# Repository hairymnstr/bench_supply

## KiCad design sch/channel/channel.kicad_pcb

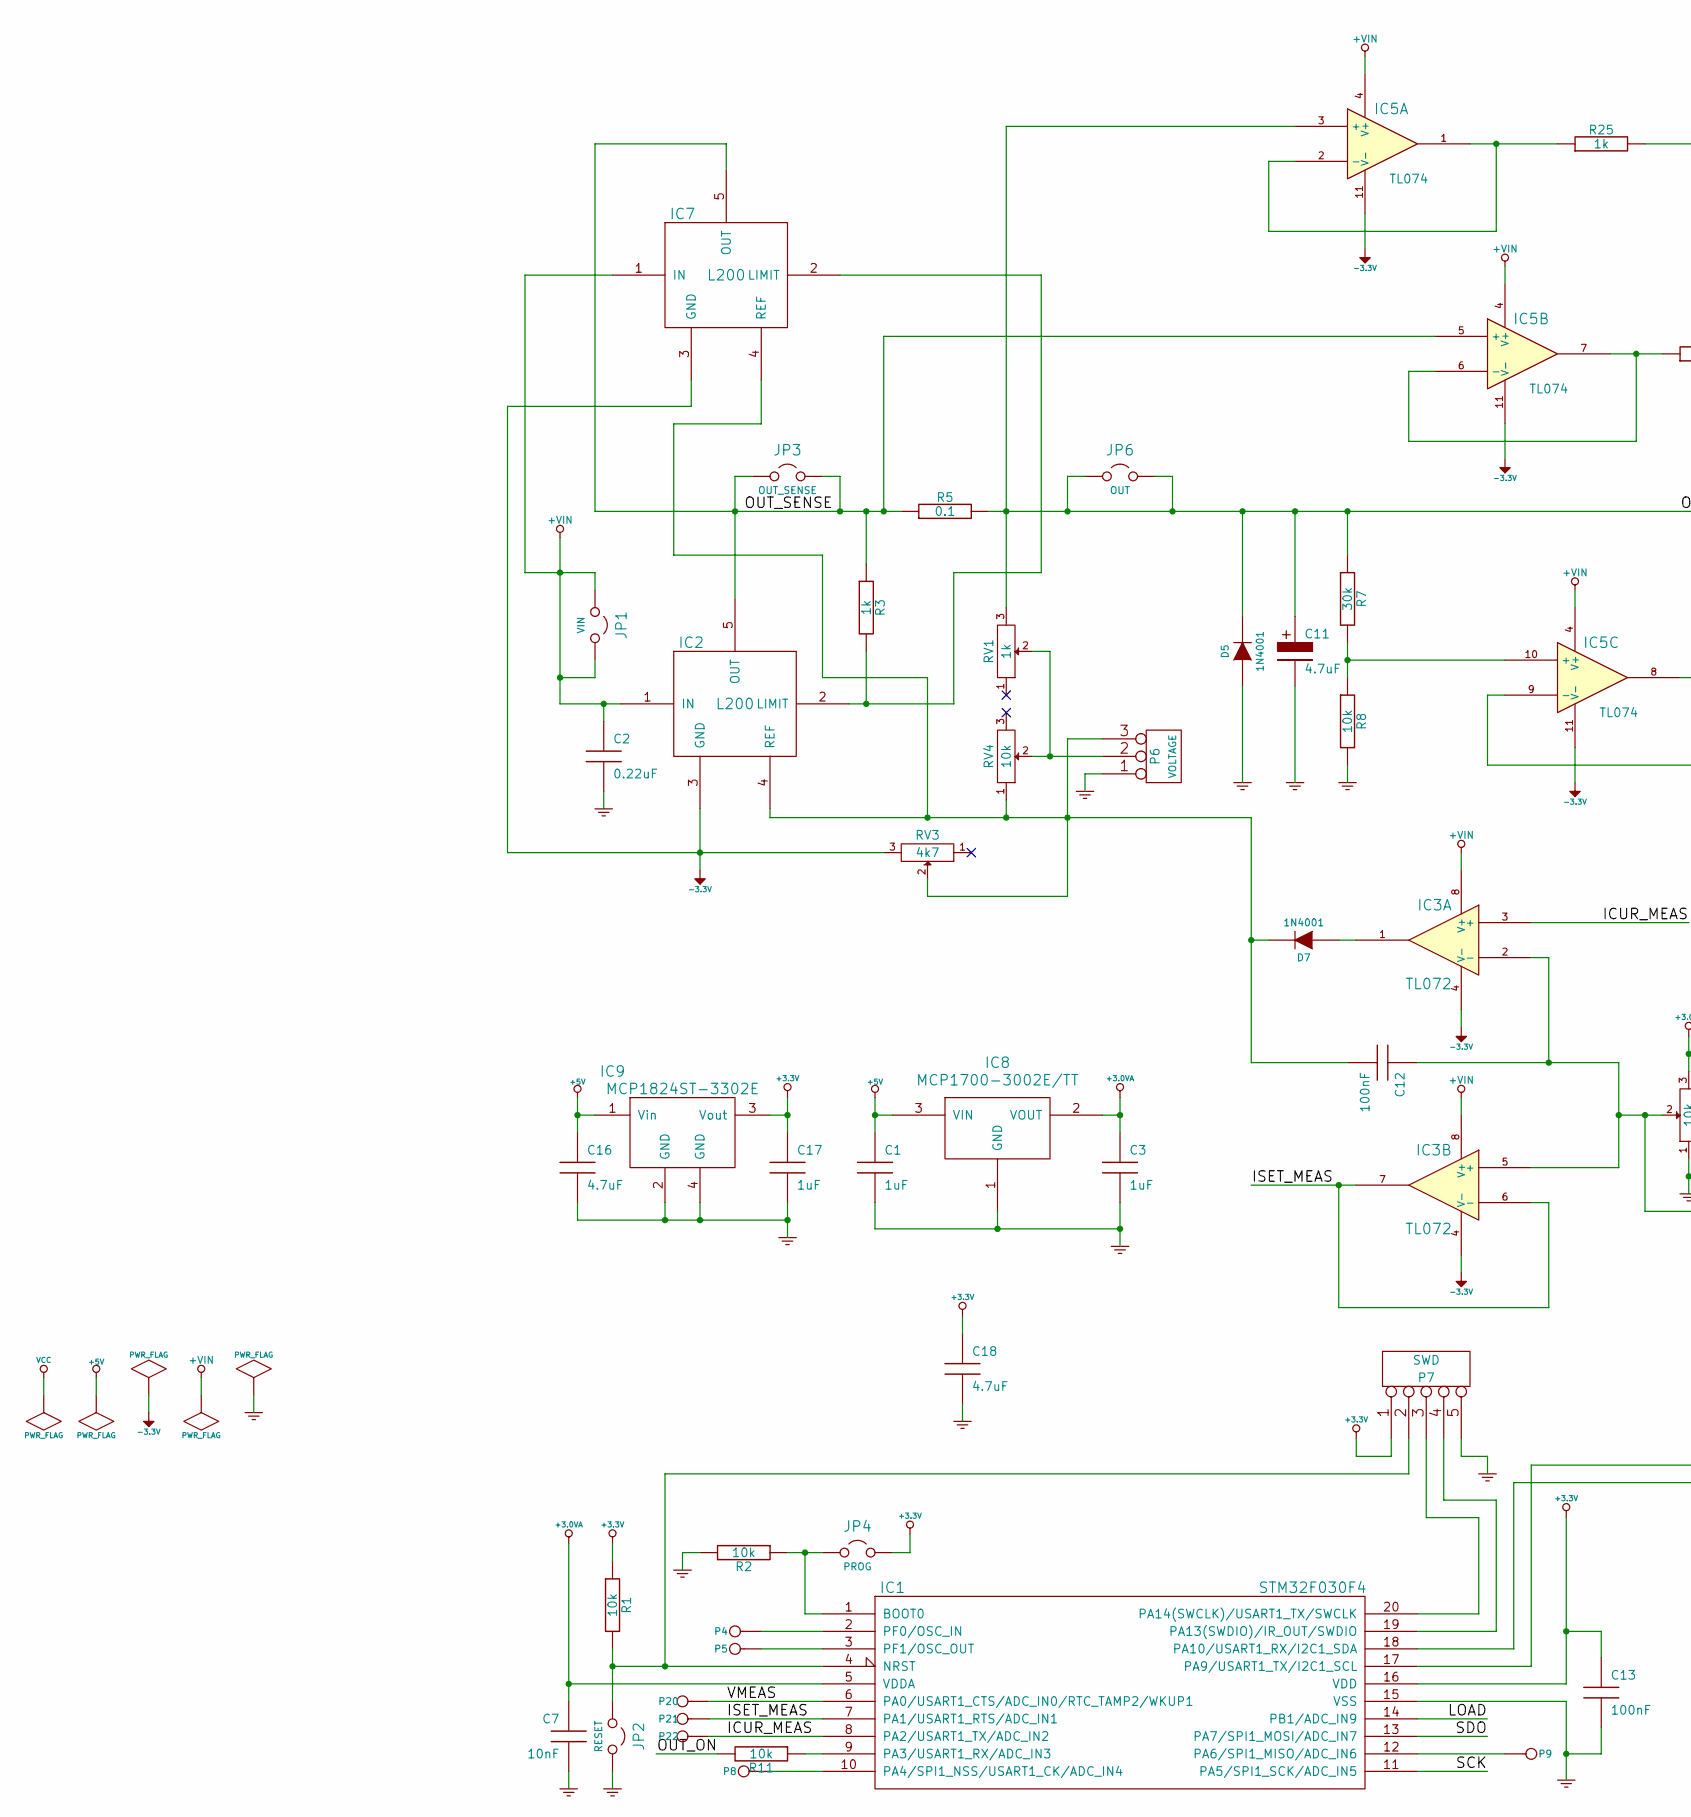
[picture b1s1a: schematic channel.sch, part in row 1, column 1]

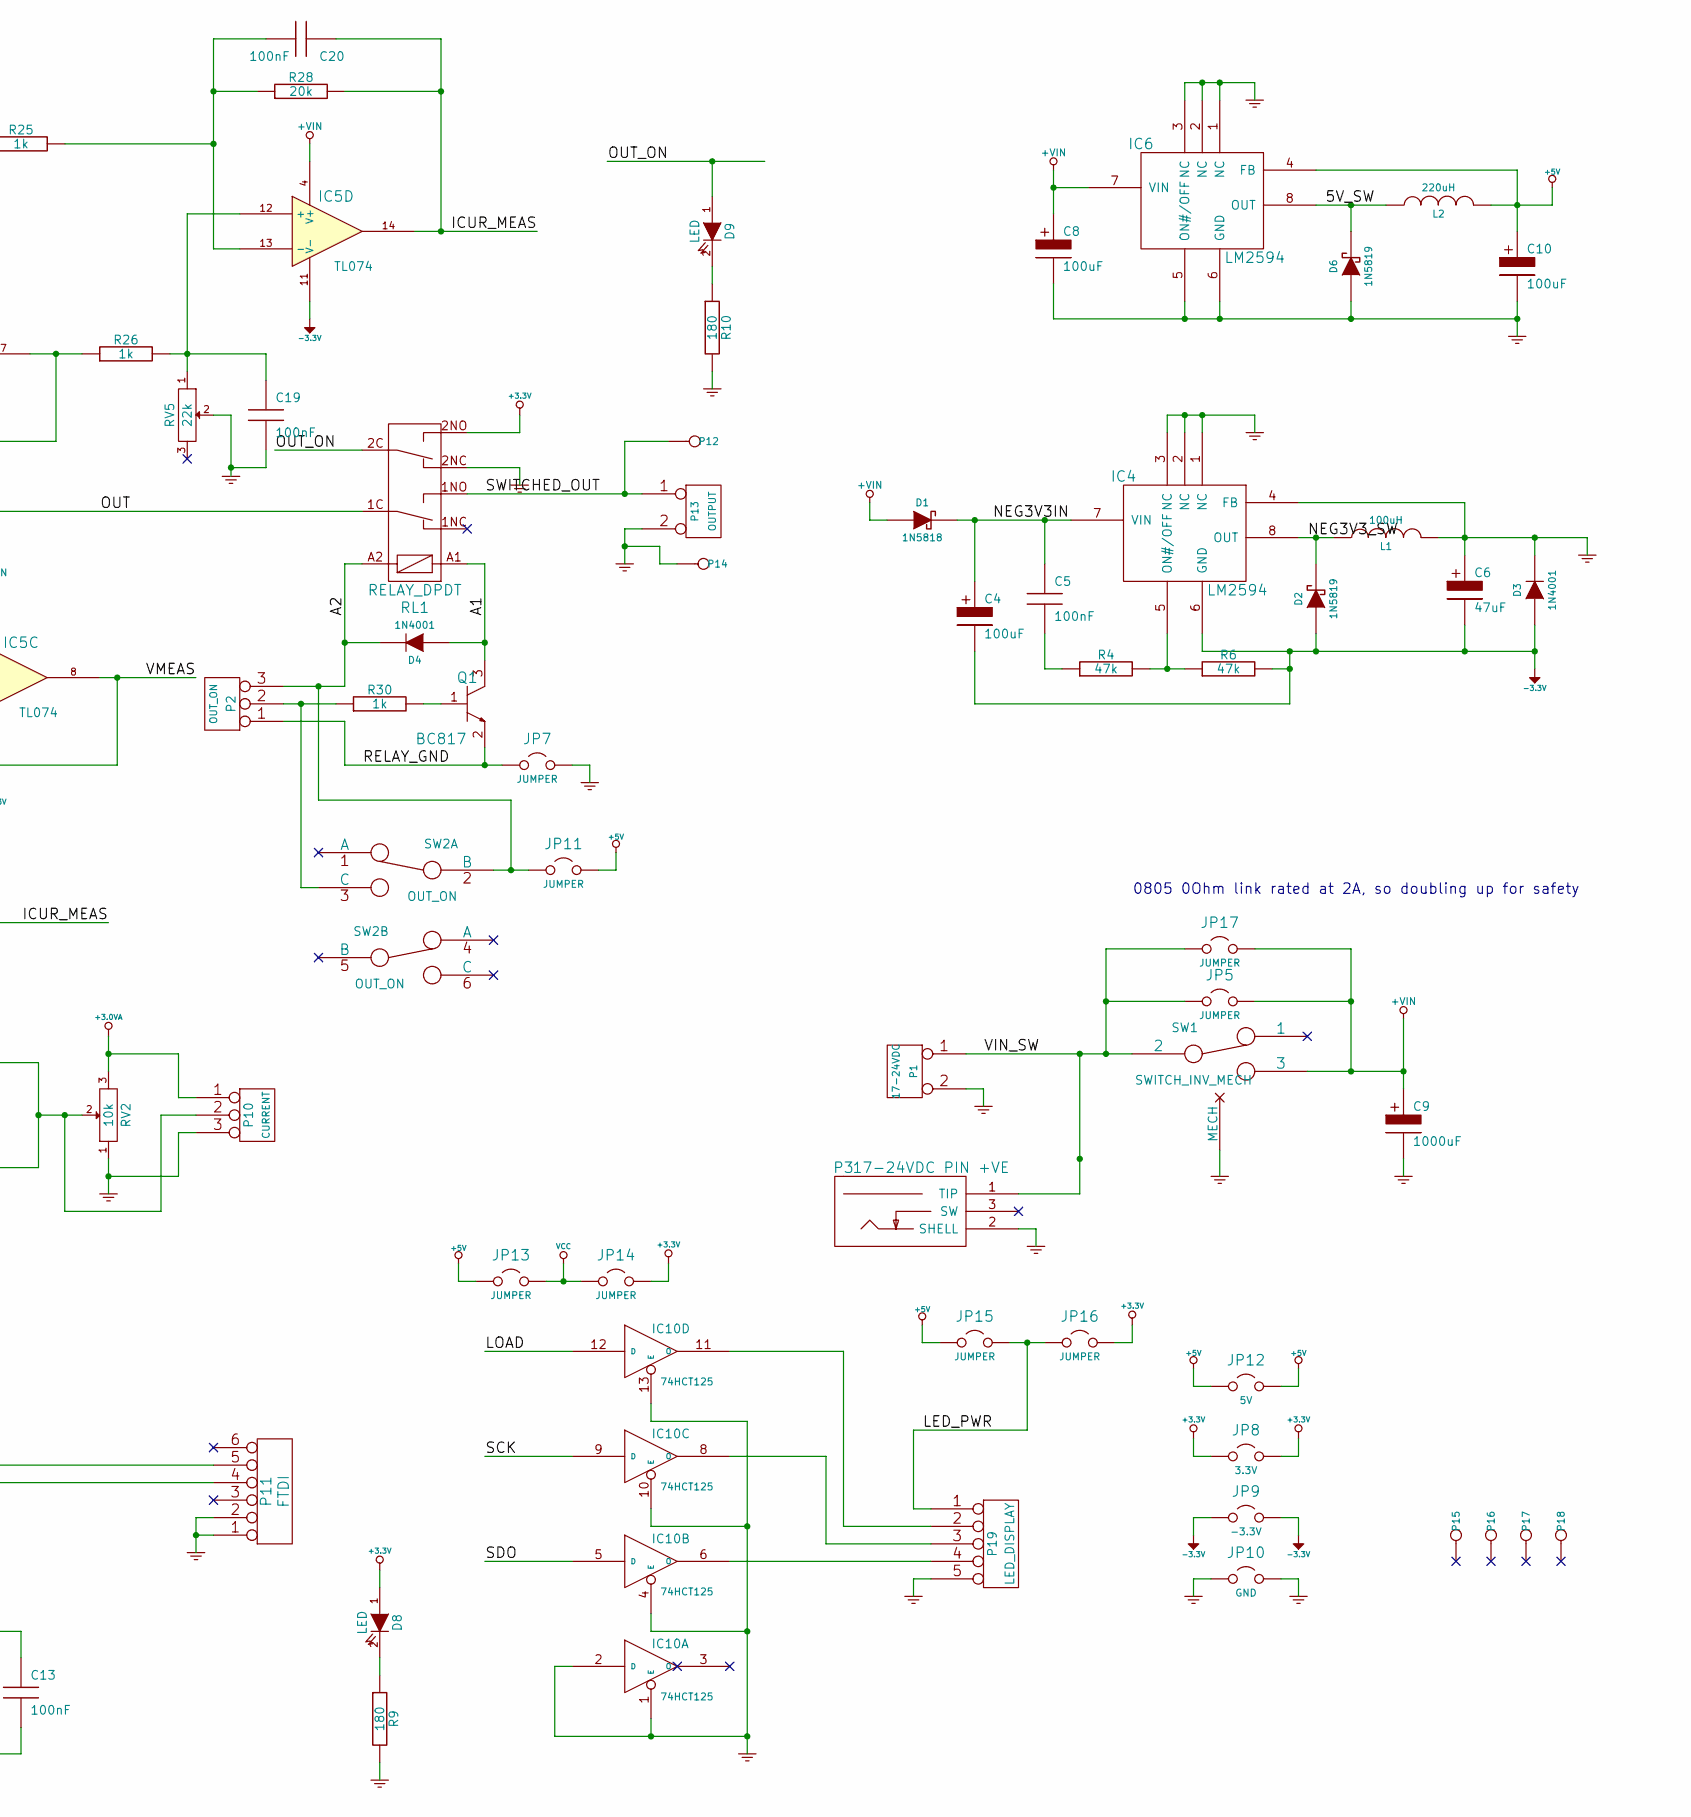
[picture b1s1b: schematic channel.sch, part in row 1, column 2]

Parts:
C1, C3, C17: 1uF
C2: 0.22uF
C4, C8, C10: 100uF
C5, C12, C13, C19, C20: 100nF
C6: 47uF
C7: 10nF
C9: 1000uF
C11, C16, C18: 4.7uF
D1: 1N5818
D2, D6: 1N5819
D3, D4, D5, D7: 1N4001
D8, D9: LED
IC1: STM32F030F4
IC2, IC7: L200
IC3: TL072; Farnell 156-4343
IC4, IC6: LM2594
IC5: TL074; Farnell 959-3349
IC8: MCP1700-3002E/TT
IC9: MCP1824ST-3302E
IC10: 74HCT125; Farnell 120-1306
JP1: VIN
JP2: RESET
JP3: OUT_SENSE
JP4: PROG
JP5, JP7, JP11, JP13, JP14, JP15, JP16, JP17: JUMPER
JP6: OUT
JP8: 3.3V
JP9: -3.3V
JP10: GND
JP12: 5V
L1: 100uH
L2: 220uH
P1: 17-24VDC
P2: OUT_ON
P3: 17-24VDC PIN +VE
P4, P5, P8, P9, P12, P14, P15, P16, P17, P18: CONN_1
P6: VOLTAGE
P7: SWD
P10: CURRENT
P11: FTDI
P13: OUTPUT
P19: LED_DISPLAY
P20: V
P21: I_SET
P22: I_NOW
Q1: BC817
R1, R2, R8, R11: 10k
R3, R25, R26, R30: 1k
R4, R6: 47k
R5: 0.1
R7: 30k
R9, R10: 180
R28: 20k
RL1: RELAY_DPDT
RV1: 1k
RV2, RV4: 10k
RV3: 4k7
RV5: 22k
SW1: SWITCH_INV_MECH
SW2: OUT_ON

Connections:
+3.0VA: C3.1, C7.1, IC1.5 (VDDA), IC8.2 (VOUT), P10.1, RV2.3
+3.3V: C13.1, C17.1, C18.1, D8.1 (A), IC1.16 (VDD), IC9.3 (Vout), JP4.2, JP8.1, JP8.2, JP14.2, JP16.2, P7.1, R1.1, RL1.2NO
+5V: C1.1, C10.1, C16.1, IC6.4 (FB), IC8.3 (VIN), IC9.1 (Vin), JP11.2, JP12.1, JP12.2, JP13.1, JP15.1, L2.2
+VIN: C2.1, C8.1, C9.1, D1.1 (A), IC2.1 (IN), IC3.8 (V+), IC5.4 (V+), IC6.7 (VIN), IC7.1 (IN), JP1.1, JP1.2, JP5.2, JP17.2, SW1.3
-3.3V: C4.2, C6.2, D2.1 (A), D3.1 (A), IC2.3 (GND), IC3.4 (V-), IC4.6 (GND), IC5.11 (V-), IC7.3 (GND), JP9.1, JP9.2, R6.2, RV3.3
/5V_SW: D6.2 (K), IC6.8 (OUT), L2.1
/A1: D4.1 (A), Q1.3 (C), RL1.A1
/A2: D4.2 (K), JP11.1, P2.3, RL1.A2, SW2.2 (B)
/ICUR_MEAS: C20.1, IC1.8 (PA2/USART1_TX/ADC_IN2), IC3.3 (+), IC5.14, P22.1, R28.2
/ISET_MEAS: IC1.7 (PA1/USART1_RTS/ADC_IN1), IC3.6 (-), IC3.7, P21.1
/LED_PWR: JP15.2, JP16.1, P19.1
/LOAD: IC1.14 (PB1/ADC_IN9), IC10.12 (D)
/NEG3V3IN: C4.1, C5.1, D1.2 (K), IC4.7 (VIN)
/NEG3V3_SW: D2.2 (K), IC4.8 (OUT), L1.1
/OUT: C11.1, D5.2 (K), IC5.3 (+), JP6.1, JP6.2, R5.2, R7.1, RL1.1C, RV1.3
/OUT_ON: D9.1 (A), R11.2, RL1.2C
/OUT_SENSE: IC2.5 (OUT), IC5.5 (+), IC7.5 (OUT), JP3.1, JP3.2, R3.1, R5.1
/RELAY_GND: JP7.1, P2.1, Q1.2 (E)
/SCK: IC1.11 (PA5/SPI1_SCK/ADC_IN5), IC10.9 (D)
/SDO: IC1.13 (PA7/SPI1_MOSI/ADC_IN7), IC10.5 (D)
/SWITCHED_OUT: P12.1, P13.1, RL1.1NO
/VIN_SW: JP5.1, JP17.1, P1.1, P3.1 (TIP), SW1.2
/VMEAS: IC1.6 (PA0/USART1_CTS/ADC_IN0/RTC_TAMP2/WKUP1), IC5.8, IC5.9 (-), P20.1
GND: C1.2, C2.2, C3.2, C6.1, C7.2, C8.2, C9.2, C10.2, C11.2, C13.2, C16.2, C17.2, C18.2, C19.2, D3.2 (K), D5.1 (A), D6.1 (A), IC1.15 (VSS), IC4.1 (NC), IC4.2 (NC), IC4.3 (NC), IC4.4 (FB), IC6.1 (NC), IC6.2 (NC), IC6.3 (NC), IC6.5 (ON#/OFF), IC6.6 (GND), IC8.1 (GND), IC9.2 (GND), IC9.4 (GND), IC10.1 (E), IC10.2 (D), IC10.4 (E), IC10.7 (GND), IC10.10 (E), IC10.13 (E), JP2.2, JP7.2, JP10.1, JP10.2, L1.2, P1.2 (PM), P3.2 (SHELL), P6.1, P7.5, P10.3, P11.1, P11.2, P13.2 (PM), P14.1, P19.5, R2.2, R8.2, R9.2, R10.2, RL1.2NC, RV2.1, RV2.GND, RV4.GND, RV5.2, SW1.4 (MECH)
unnamed: C5.2, R4.1
unnamed: C12.1, IC3.2 (-), IC3.5 (+), P10.2 (PM), RV2.2
unnamed: C12.2, D7.2 (K), IC2.4 (REF), IC7.4 (REF), P6.3, RV3.2, RV4.1
unnamed: C19.1, IC5.12 (+), R26.2, RV5.1
unnamed: C20.2, IC5.13 (-), R25.2, R28.1
unnamed: D7.1 (A), IC3.1
unnamed: D8.2 (K), R9.1
unnamed: D9.2 (K), R10.1
unnamed: IC1.1 (BOOT0), JP4.1, R2.1
unnamed: IC1.2 (PF0/OSC_IN), P4.1
unnamed: IC1.3 (PF1/OSC_OUT), P5.1
unnamed: IC1.4 (NRST), JP2.1, P7.2, R1.2
unnamed: IC1.9 (PA3/USART1_RX/ADC_IN3), R11.1
unnamed: IC1.10 (PA4/SPI1_NSS/USART1_CK/ADC_IN4), P8.1
unnamed: IC1.12 (PA6/SPI1_MISO/ADC_IN6), P9.1
unnamed: IC1.17 (PA9/USART1_TX/I2C1_SCL), P11.5
unnamed: IC1.18 (PA10/USART1_RX/I2C1_SDA), P11.4
unnamed: IC1.19 (PA13(SWDIO)/IR_OUT/SWDIO), P7.4
unnamed: IC1.20 (PA14(SWCLK)/USART1_TX/SWCLK), P7.3
unnamed: IC2.2 (LIMIT), IC7.2 (LIMIT), R3.2
unnamed: IC4.5 (ON#/OFF), R4.2, R6.1
unnamed: IC5.1, IC5.2 (-), R25.1
unnamed: IC5.6 (-), IC5.7, R26.1
unnamed: IC5.10 (+), R7.2, R8.1
unnamed: IC10.6 (O), P19.4
unnamed: IC10.8 (O), P19.3
unnamed: IC10.11 (O), P19.2
unnamed: P2.2 (PM), R30.1, SW2.3 (C)
unnamed: P6.2 (PM), RV1.2, RV4.2
unnamed: Q1.1 (B), R30.2
VCC: IC10.14 (VCC), JP13.2, JP14.1

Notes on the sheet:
0805 0Ohm link rated at 2A, so doubling up for safety

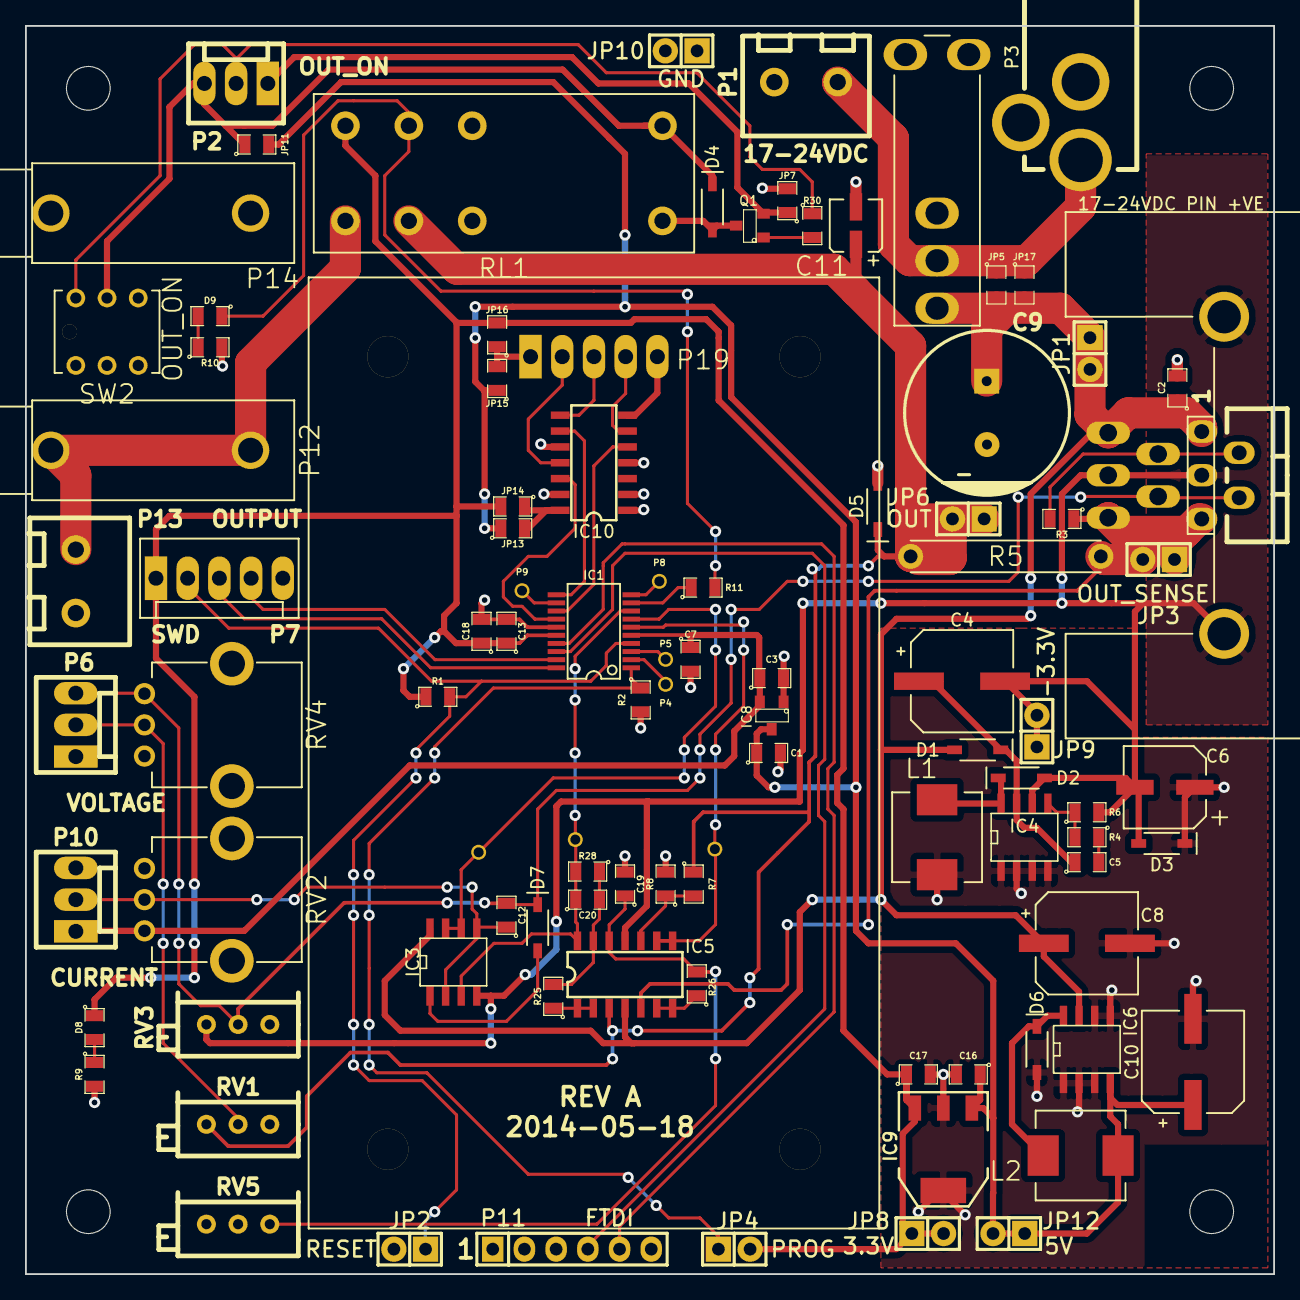
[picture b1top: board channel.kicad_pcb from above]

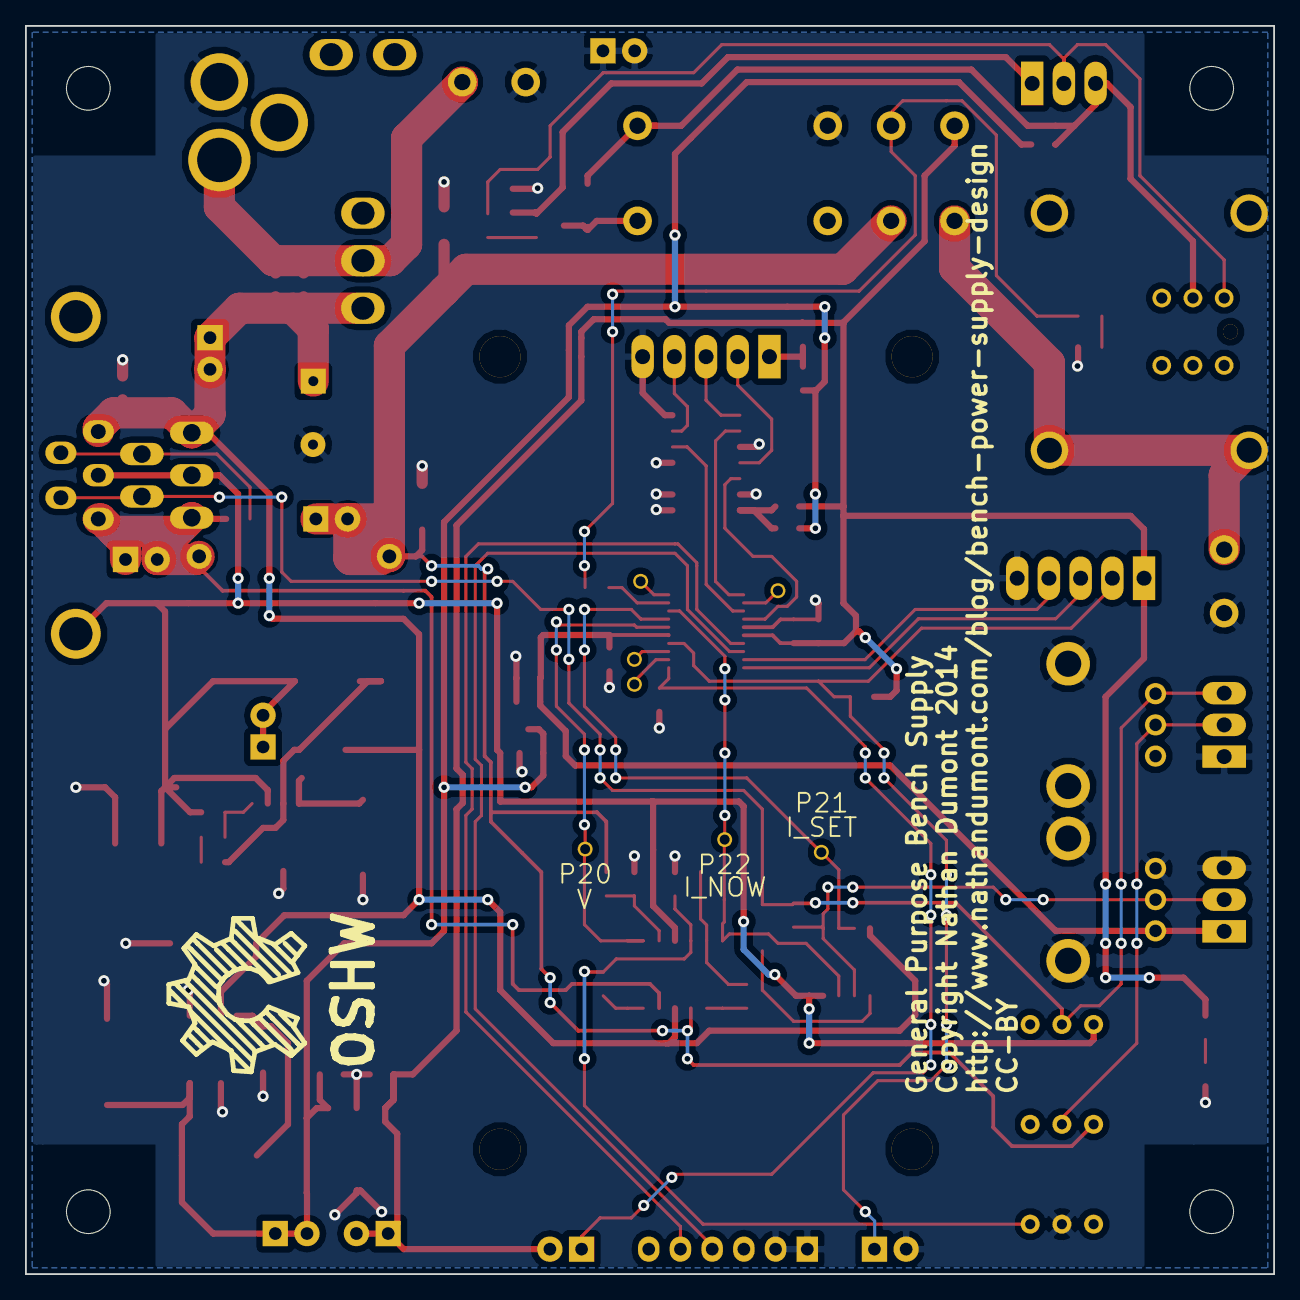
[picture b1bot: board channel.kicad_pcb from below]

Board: 2 copper layers, 100.0 x 100.0 mm, 103 parts (4 on the bottom side), 55 nets.

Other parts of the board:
Sym: Symbol_OSHW-Logo_SilkScreen_BIG_07Jul2012; Symbol_OSHW-Logo_SilkScreen_BIG

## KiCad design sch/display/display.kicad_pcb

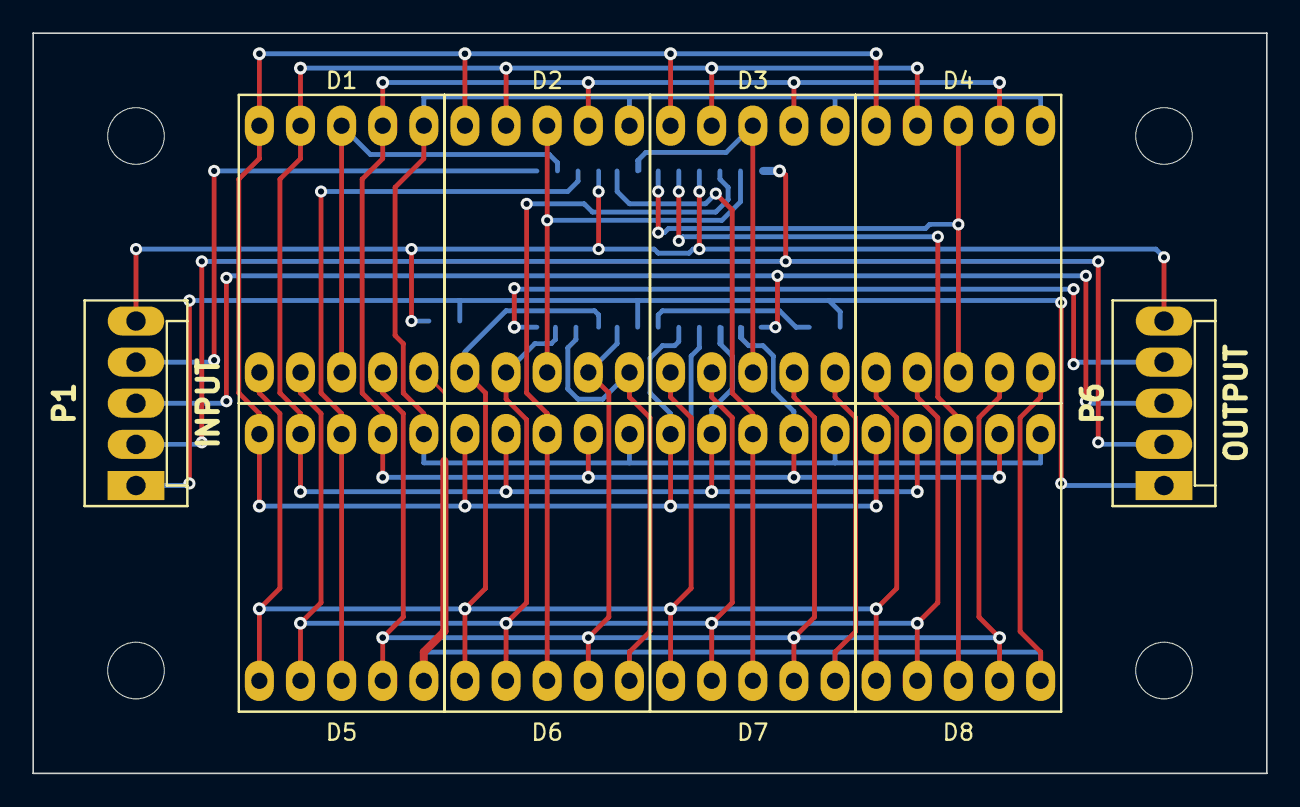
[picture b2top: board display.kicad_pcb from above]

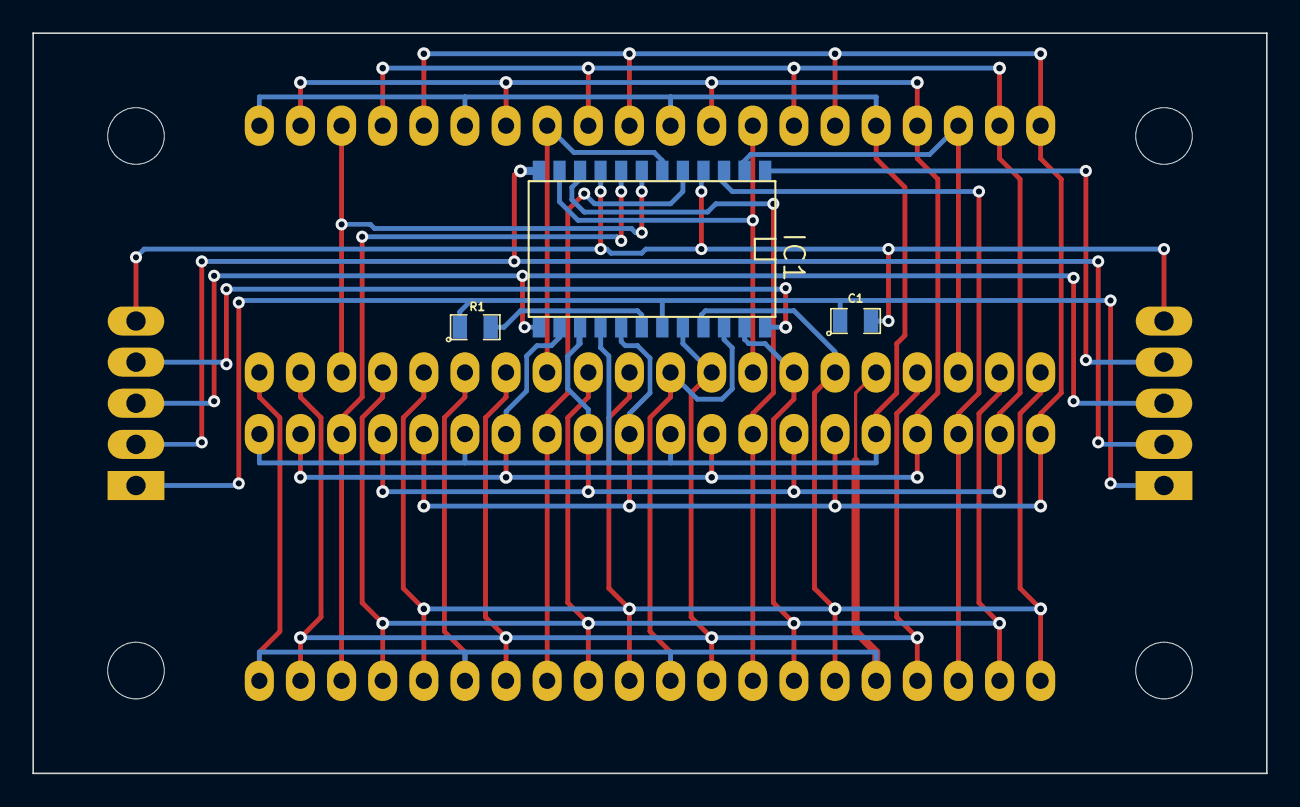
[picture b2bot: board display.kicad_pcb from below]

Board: 2 copper layers, 76.2 x 45.7 mm, 17 parts (3 on the bottom side), 23 nets.

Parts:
C1: 100nF; SM0805
D1, D2, D3, D4, D5, D6, D7, D8: 7SEGMENTS; 7SEGM_LED_0_5_INCH
IC1: MAX7219; SOIC24-WIDE
P1: INPUT; MOLEX_KK_5
P2, P3, P4, P5: CONN_1; MountingHole_3-5mm
P6: OUTPUT; MOLEX_KK_5
R1: 27k; SM0805

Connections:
+5V: C1.1, IC1.19, P1.1, P6.1, R1.1
/DI: IC1.1, P1.4
/DIG0: D1.3, D1.8, IC1.2
/DIG1: D2.3, D2.8, IC1.11
/DIG2: D3.3, D3.8, IC1.6
/DIG3: D4.3, D4.8, IC1.7
/DIG4: D5.3, D5.8, IC1.3
/DIG5: D6.3, D6.8, IC1.10
/DIG6: D7.3, D7.8, IC1.5
/DIG7: D8.3, D8.8, IC1.8
/DO: IC1.24, P6.4
/LOAD: IC1.12, P1.2, P6.2
/SCK: IC1.13, P1.3, P6.3
/SEGA: D1.7, D2.7, D3.7, D4.7, D5.7, D6.7, D7.7, D8.7, IC1.14
/SEGB: D1.6, D2.6, D3.6, D4.6, D5.6, D6.6, D7.6, D8.6, IC1.16
/SEGC: D1.4, D2.4, D3.4, D4.4, D5.4, D6.4, D7.4, D8.4, IC1.20
/SEGD: D1.2, D2.2, D3.2, D4.2, D5.2, D6.2, D7.2, D8.2, IC1.23
/SEGDP: D1.5, D2.5, D3.5, D4.5, D5.5, D6.5, D7.5, D8.5, IC1.22
/SEGE: D1.1, D2.1, D3.1, D4.1, D5.1, D6.1, D7.1, D8.1, IC1.21
/SEGF: D1.9, D2.9, D3.9, D4.9, D5.9, D6.9, D7.9, D8.9, IC1.15
/SEGG: D1.10, D2.10, D3.10, D4.10, D5.10, D6.10, D7.10, D8.10, IC1.17
GND: C1.2, IC1.4, IC1.9, P1.5, P6.5
unnamed: IC1.18, R1.2

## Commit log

2014-05-05 Initial commit.
2014-05-05 Updated the channel schematic to new design. Ready to start on footprint assignment.
2014-05-07 Started assigning footprints for components
2014-05-09 Associating some more footprints
2014-05-10 More footprints associated. Not done yet :(
2014-05-10 Fully assigned components, changed the design to remove opto-coupler, using relay instead
2014-05-11 Fully laid out PCB. Needs a bit of tweaking for optimisation, and silk screen isn't done yet.
2014-05-11 A few tweaks to improve the layout. Still not sorted silk screen.
2014-05-12 Started designing the display board
2014-05-13 Started laying out the LED carrier PCB
2014-05-15 Finished layout of the display. Not really happy with it though.
2014-05-17 Fiddling with the layout of the display to make it more elegant.
2014-05-17 Happy with the display module now. Not done gerbers/drill yet but layout is done incl. silk screen.
2014-05-17 Started ripping up the channel board to add a heatsink for standalone mode, and switch the display around so it faces the right way.
2014-05-17 More or less happy with the channel PCB. Needs silk screen sorting out.
2014-05-18 Final changes before ordering PCBs

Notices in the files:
sch/channel/channel.kicad_pcb:
Copyright Nathan Dumont 2014
CC-BY
